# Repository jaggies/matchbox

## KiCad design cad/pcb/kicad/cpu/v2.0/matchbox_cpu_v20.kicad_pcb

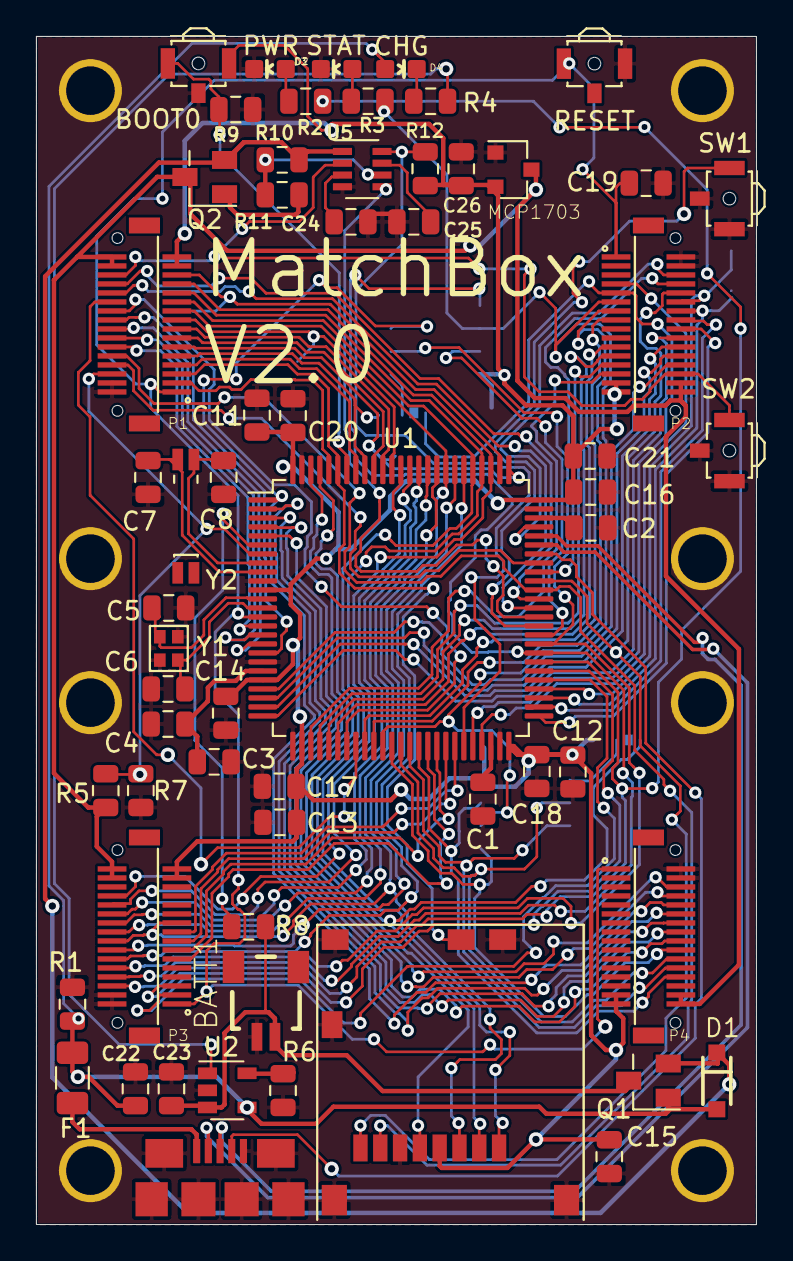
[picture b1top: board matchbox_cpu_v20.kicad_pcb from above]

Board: 6 copper layers, 40.0 x 66.0 mm, 75 parts (0 on the bottom side), 107 nets.

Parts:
BATT1: SM02B-SRSS-TBS; SM02B-SRSS-TB
C1, C2: 2.2uF; C_0805_2012Metric
C3, C9, C10, C11, C12, C13, C15, C21, C25, C26: 1uF; C_0805_2012Metric
C4, C14, C16, C17, C18, C19, C20: 0.1uF; C_0805_2012Metric
C5, C6: 4pF; C_0805_2012Metric
C7, C8: 8pF; C_0805_2012Metric
C22, C23: 10uF; C_0805_2012Metric
C24: .033uF; C_0805_2012Metric
D1: MBR120; SOD-123
D2: PWR; LED-0603
D3: STAT; LED-0603
D4: CHG; LED-0603
F1: PTCTHERMISTOR1206; R_1206_3216Metric
JP1: BANK1_SEL; SolderJumper-3_P1.3mm_Bridged12_Pad1.0x1.5mm_NumberLabels
JP2: BANK2_SEL; SolderJumper-3_P1.3mm_Bridged12_Pad1.0x1.5mm_NumberLabels
P1, P2, P3, P4: DF12-32-DP
Q1, Q2: FDN360P; SuperSOT-3
R1, R6: 4.7k; R_0805_2012Metric
R2, R3, R4: 1k; R_0805_2012Metric
R5, R7, R9, R12: 10k; R_0805_2012Metric
R8, R10, R11: 100k; R_0805_2012Metric
SD1: MOLEX_MICROSD_PP
SW0: BOOT0; B3U-3100PM-B
SW1, SW2: B3U-3100PM-B
SW3: RESET; B3U-3100PM-B
TP1: VCC_3V3; TestPoint_Pad_D1.5mm
TP2: GND; TestPoint_Pad_D1.5mm
TP3: RESET; TestPoint_Pad_D1.5mm
TP4: SWDCLK/TCK; TestPoint_Pad_D1.5mm
TP5: SWDIO/TMS; TestPoint_Pad_D1.5mm
TP6: SWO/TDO; TestPoint_Pad_D1.5mm
TP7: TDI; TestPoint_Pad_D1.5mm
TP8: TX; TestPoint_Pad_D1.5mm
TP9: RX; TestPoint_Pad_D1.5mm
U1: STM32H753VITx; LQFP-100_14x14mm_P0.5mm
U2: MCP73831-2-OT; SOT-23-5
U3: BANK1; SOIC-8_3.9x4.9mm_P1.27mm
U4: BANK2; SOIC-8_3.9x4.9mm_P1.27mm
U5: LTC2954; SOT-23-8
U6: MCP1703; SOT-23
USB1: MICROUSB
Y1: 16MHz(9pF); ABM11
Y2: 32.768kHz (9pF); CRYSTAL-32KHZ-SMD_EPSON_MC146

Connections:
/BANK1_CS#: JP1.2, U3.1
/BANK2_CS#: JP2.2, U4.1
/BOOT0: R9.1, SW0.1, U1.94
/OSC32K_IN: C8.1, U1.8, Y2.P$2
/OSC32K_OUT: C7.1, U1.9, Y2.P$1
/OSC_IN: C5.1, U1.12, Y1.1
/OSC_OUT: C6.1, U1.13, Y1.3
/PA0: P2.26, U1.22
/PA1: P2.24, U1.23
/PA2: P2.22, U1.24
/PA3: P2.20, U1.25
/PA4: P2.27, U1.28
/PA5: P2.25, U1.29
/PA6: P2.23, U1.30
/PA7: P2.21, U1.31
/PA8: P2.8, U1.67
/PA9: P1.8, U1.68
/PA13: P2.6, TP5.1, U1.72
/PA14: P1.11, TP4.1, U1.76
/PA15: P1.27, TP7.1, U1.77
/PB0: P2.15, U1.34
/PB1: P2.13, U1.35
/PB2: P2.11, R3.2, U1.36, U3.6, U4.6
/PB3: P1.17, TP6.1, U1.89
/PB4: P1.15, U1.90
/PB5: P1.13, U1.91
/PB6: JP1.3, P1.9, U1.92
/PB7: P1.7, U1.93
/PB8: P1.5, SD1.DET, U1.95
/PB9: P1.3, U1.96
/PB10: JP1.1, P2.9, U1.46
/PB11: P2.7, U1.47
/PB12: P2.18, U1.51
/PB13: P2.16, U1.52
/PB14: P2.14, TP8.1, U1.53
/PB15: P2.12, TP9.1, U1.54
/PC0: P1.12, U1.15
/PC1: P1.14, U1.16
/PC2: P1.16, U1.17
/PC3: P1.18, U1.18
/PC4: P1.20, U1.32
/PC5: P1.22, U1.33
/PC6: P1.24, U1.63
/PC7: P1.26, U1.64
/PC8: P1.10, SD1.7, U1.65
/PC9: P2.10, SD1.8, U1.66
/PC10: P1.25, SD1.1, U1.78
/PC11: JP2.1, P1.23, SD1.2, U1.79
/PC12: P1.21, SD1.5, U1.80
/PC13: P1.6, R5.2, R7.1, U1.7
/PD0: P3.12, U1.81
/PD1: P3.14, U1.82
/PD2: P1.19, P3.16, P3.19, SD1.3, U1.83
/PD3: P3.18, U1.84
/PD4: P3.20, U1.85
/PD5: P3.22, U1.86
/PD6: P3.24, U1.87
/PD7: P3.26, U1.88
/PD8: P3.3, U1.55
/PD9: P3.5, U1.56
/PD10: P3.6, R2.2, U1.57
/PD11: P3.8, U1.58, U3.5
/PD12: P3.10, U1.59, U3.2
/PD13: U1.60, U3.7
/PD14: SW1.1, U1.61
/PD15: U1.62, U5.5
/PE0: P4.6, U1.97
/PE1: P4.8, U1.98
/PE2: P4.10, U1.1, U3.3
/PE3: P4.12, U1.2
/PE4: P4.14, U1.3
/PE5: P4.16, U1.4
/PE6: P4.18, U1.5
/PE7: P4.20, U1.37, U4.5
/PE8: P4.22, U1.38, U4.2
/PE9: P4.24, U1.39, U4.3
/PE10: P4.26, U1.40, U4.7
/PE11: P3.11, U1.41
/PE12: P3.13, U1.42
/PE13: P3.15, U1.43
/PE14: P3.17, U1.44
/PE15: R12.1, U1.45, U5.8
/PWR_ON: P1.28, P2.28, SW2.1, U5.2
/RESET#: C19.1, P1.1, P2.1, P3.1, P4.1, SW3.1, TP3.1, U1.14
/STAT: R4.2, U2.1
/USB_D+: U1.71, USB1.3
/USB_D-: U1.70, USB1.2
/USB_ID: U1.69, USB1.4
/VBAT: BATT1.1, C23.1, Q1.3, R8.1, U2.3
/VCC: P1.30, P1.32, P2.30, P2.32, P3.30, P3.32, P4.30, P4.32, Q2.3, R5.1, U6.3
/VCC_3V3: C9.1, C10.1, C11.1, C12.1, C13.1, C14.1, C15.1, C16.1, C17.1, C18.1, C20.1, C21.1, C26.1, JP2.3, P1.29, P1.31, P2.29, P2.31, P3.29, P3.31, P4.29, P4.31, R12.2, SD1.4, SW0.2, TP1.1, U1.11, U1.21, U1.27, U1.50, U1.75, U1.100, U3.8, U4.8, U6.2
/VCC_BKUP: R8.2, U1.6
/VCC_SEL: D1.C, Q1.2, Q2.2, R10.1, U5.1
/VCC_USB: F1.1, USB1.1
/VCC_USBF: C22.1, D1.A, D4.A, F1.2, Q1.1, R1.1, U2.4
/VREF: C3.1, C4.1, U1.20
GND: BATT1.2, C1.1, C2.1, C3.2, C4.2, C5.2, C6.2, C7.2, C8.2, C9.2, C10.2, C11.2, C12.2, C13.2, C14.2, C15.2, C16.2, C17.2, C18.2, C19.2, C20.2, C21.2, C22.2, C23.2, C24.2, C25.2, C26.2, D2.C, D3.C, P1.2, P1.4, P2.2, P2.4, P3.2, P3.4, P4.2, P4.4, R1.2, R6.1, R7.2, R9.2, SD1.6, SD1.M1, SD1.M2, SD1.M3, SD1.M4, SD1.M5, SW0.GND, SW1.2, SW1.GND, SW2.2, SW2.GND, SW3.2, TP2.1, U1.10, U1.19, U1.26, U1.49, U1.74, U1.99, U2.2, U3.4, U4.4, U5.4, U6.1, USB1.5, USB1.6, USB1.7, USB1.8, USB1.9, USB1.10, USB1.11, Y1.2, Y1.4
unnamed: C1.2, U1.48
unnamed: C2.2, U1.73
unnamed: C24.1, U5.3
unnamed: C25.1, U5.7
unnamed: D2.A, R2.1
unnamed: D3.A, R3.1
unnamed: D4.C, R4.1
unnamed: Q2.1, R11.1
unnamed: R6.2, U2.5
unnamed: R10.2, R11.2, U5.6

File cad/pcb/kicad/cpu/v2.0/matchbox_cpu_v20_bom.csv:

Comment,Designator,Footprint,LCSC
"SM02B-SRSS-TBS","BATT1","matchbox_cpu_v20:SM02B-SRSS-TB",""
"2.2uF","C1,C2","Capacitor_SMD:C_0805_2012Metric",""
"0.1uF","C4,C14,C16,C17,C18,C19,C20","Capacitor_SMD:C_0805_2012Metric",""
"10uF","C22,C23","Capacitor_SMD:C_0805_2012Metric",""
".033uF","C24","Capacitor_SMD:C_0805_2012Metric",""
"1uF","C3,C9,C10,C11,C12,C13,C15,C21,C25,C26","Capacitor_SMD:C_0805_2012Metric",""
"4pF","C5,C6","Capacitor_SMD:C_0805_2012Metric",""
"8pF","C7,C8","Capacitor_SMD:C_0805_2012Metric",""
"MBR120","D1","Diode_SMD:D_SOD-123","C223608"
"CHG","D4","LED_SMD:LED_0603_1608Metric"," C72043"
"PTCTHERMISTOR1206","F1","Resistor_SMD:R_1206_3216Metric","C69688"
"BANK1_SEL","JP1","Jumper:SolderJumper-3_P1.3mm_Bridged12_Pad1.0x1.5mm_NumberLabels",""
"BANK2_SEL","JP2","Jumper:SolderJumper-3_P1.3mm_Bridged12_Pad1.0x1.5mm_NumberLabels",""
"PWR","LED2","LED_SMD:LED_0603_1608Metric",""
"STAT","LED3","LED_SMD:LED_0603_1608Metric"," C72043"
"DF12-32-DP","P1,P2,P3,P4","matchbox_cpu_v20:DF12-32-DP",""
"FDN360P","Q1,Q2","Package_TO_SOT_SMD:SuperSOT-3","C124463"
"1k","R2,R3,R4","Resistor_SMD:R_0805_2012Metric",""
"4.7k","R1,R6","Resistor_SMD:R_0805_2012Metric",""
"100k","R8,R10,R11","Resistor_SMD:R_0805_2012Metric",""
"10k","R5,R7,R9,R12","Resistor_SMD:R_0805_2012Metric",""
"MOLEX_MICROSD_PP","SD1","matchbox_ble_v01:MOLEX_MICROSD_PP","C429846"
"BOOT0","SW0","matchbox_cpu_v20:B3U-3100PM-B",""
"B3U-3100PM-B","SW1,SW2","matchbox_cpu_v20:B3U-3100PM-B",""
"RESET","SW3","matchbox_cpu_v20:B3U-3100PM-B",""
"VCC_3V3","TP1","TestPoint:TestPoint_Pad_D1.5mm",""
"GND","TP2","TestPoint:TestPoint_Pad_D1.5mm",""
"RESET","TP3","TestPoint:TestPoint_Pad_D1.5mm",""
"SWDCLK/TCK","TP4","TestPoint:TestPoint_Pad_D1.5mm",""
"SWDIO/TMS","TP5","TestPoint:TestPoint_Pad_D1.5mm",""
"SWO/TDO","TP6","TestPoint:TestPoint_Pad_D1.5mm",""
"TDI","TP7","TestPoint:TestPoint_Pad_D1.5mm",""
"TX","TP8","TestPoint:TestPoint_Pad_D1.5mm",""
"RX","TP9","TestPoint:TestPoint_Pad_D1.5mm",""
"STM32H753VITx","U1","Package_QFP:LQFP-100_14x14mm_P0.5mm","C529058"
"MCP73831-2-OT","U2","Package_TO_SOT_SMD:SOT-23-5","C424093"
"BANK1","U3","Package_SO:SOIC-8_3.9x4.9mm_P1.27mm","C113767"
"BANK2","U4","Package_SO:SOIC-8_3.9x4.9mm_P1.27mm","C113767"
"LTC2954","U5","Package_TO_SOT_SMD:SOT-23-8","C683782"
"MCP1703","U6","Package_TO_SOT_SMD:SOT-23","C638602"
"MICROUSB","USB1","matchbox_cpu_v20:MICROUSB","C132564"
"16MHz(9pF)","Y1","matchbox_cpu_v20:ABM11"," C13738"
"32.768kHz (9pF)","Y2","matchbox_cpu_v20:CRYSTAL-32KHZ-SMD_EPSON_MC146"," C15482"

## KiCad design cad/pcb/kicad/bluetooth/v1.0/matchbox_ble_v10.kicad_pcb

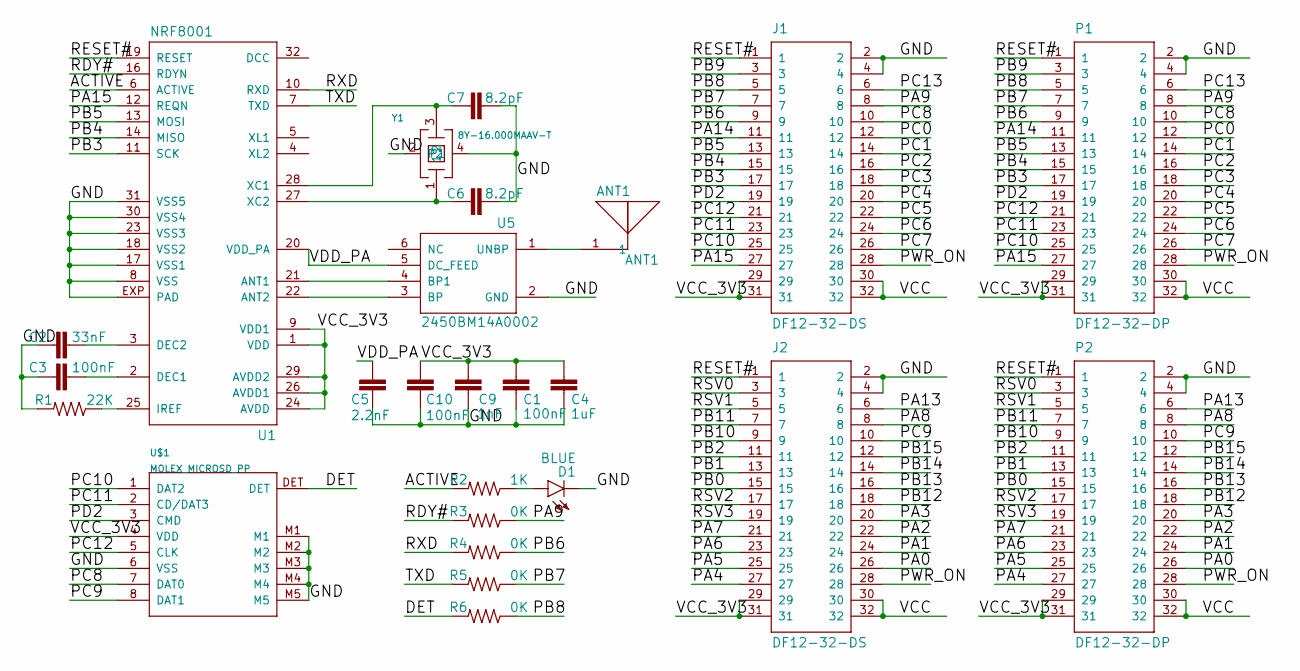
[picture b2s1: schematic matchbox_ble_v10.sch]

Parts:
ANT1: ANT1; 2450AT18A100; PARTNO AS-ITM-00132
C1, C3, C10: 100nF; 0402-CAP; MPN 1C20Z5U104M050B
C2: 33nF; 0402-CAP
C4: 1uF; 0805
C5: 2.2nF; 0402-CAP
C6, C7: 8.2pF; 0402-CAP
C9: 1nF; 0402-CAP
D1: BLUE; LED-0603
J1, J2: DF12-32-DS
P1, P2: DF12-32-DP
R1: 22K; 0402-RES
R2: 1K; 0805
R3, R4, R5, R6: 0K; 0805
U1: NRF8001; ATMEL_QFN32
U5: 2450BM14A0002
U$1: MOLEX_MICROSD_PP
Y1: 8Y-16.000MAAV-T; ABM11; PARTNO AS-ITM-00228

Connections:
/ACTIVE: R2.2, U1.6 (ACTIVE)
/DET: R6.2, U$1.DET
/GND: C1.2, C2.2, C3.2, C4.2, C5.2, C6.2, C7.2, C9.2, C10.2, D1.C, J1.2, J1.4, J2.2, J2.4, P1.2, P1.4, P2.2, P2.4, R1.2, U1.8 (VSS), U1.17 (VSS1), U1.18 (VSS2), U1.23 (VSS3), U1.30 (VSS4), U1.31 (VSS5), U1.EXP (PAD), U5.2 (GND), U$1.6 (VSS), U$1.M1, U$1.M2, U$1.M3, U$1.M4, U$1.M5, Y1.2, Y1.4 (P1)
/PA0: J2.26, P2.26
/PA1: J2.24, P2.24
/PA2: J2.22, P2.22
/PA3: J2.20, P2.20
/PA4: J2.27, P2.27
/PA5: J2.25, P2.25
/PA6: J2.23, P2.23
/PA7: J2.21, P2.21
/PA8: J2.8, P2.8
/PA9: J1.8, P1.8, R3.1
/PA13: J2.6, P2.6
/PA14: J1.11, P1.11
/PA15: J1.27, P1.27, U1.12 (REQN)
/PB0: J2.15, P2.15
/PB1: J2.13, P2.13
/PB2: J2.11, P2.11
/PB3: J1.17, P1.17, U1.11 (SCK)
/PB4: J1.15, P1.15, U1.14 (MISO)
/PB5: J1.13, P1.13, U1.13 (MOSI)
/PB6: J1.9, P1.9, R4.1
/PB7: J1.7, P1.7, R5.1
/PB8: J1.5, P1.5, R6.1
/PB9: J1.3, P1.3
/PB10: J2.9, P2.9
/PB11: J2.7, P2.7
/PB12: J2.18, P2.18
/PB13: J2.16, P2.16
/PB14: J2.14, P2.14
/PB15: J2.12, P2.12
/PC0: J1.12, P1.12
/PC1: J1.14, P1.14
/PC2: J1.16, P1.16
/PC3: J1.18, P1.18
/PC4: J1.20, P1.20
/PC5: J1.22, P1.22
/PC6: J1.24, P1.24
/PC7: J1.26, P1.26
/PC8: J1.10, P1.10, U$1.7 (DAT0)
/PC9: J2.10, P2.10, U$1.8 (DAT1)
/PC10: J1.25, P1.25, U$1.1 (DAT2)
/PC11: J1.23, P1.23, U$1.2 (CD/DAT3)
/PC12: J1.21, P1.21, U$1.5 (CLK)
/PC13: J1.6, P1.6
/PD2: J1.19, P1.19, U$1.3 (CMD)
/PWR_ON: J1.28, J2.28, P1.28, P2.28
/RDY#: R3.2, U1.16 (RDYN)
/RESET#: J1.1, J2.1, P1.1, P2.1, U1.19 (RESET)
/RSV0: J2.3, P2.3
/RSV1: J2.5, P2.5
/RSV2: J2.17, P2.17
/RSV3: J2.19, P2.19
/RXD: R4.2, U1.10 (RXD)
/TXD: R5.2, U1.7 (TXD)
/VCC: J1.30, J1.32, J2.30, J2.32, P1.30, P1.32, P2.30, P2.32
/VCC_3V3: C1.1, C4.1, C9.1, C10.1, J1.29, J1.31, J2.29, J2.31, P1.29, P1.31, P2.29, P2.31, U1.1 (VDD), U1.9 (VDD1), U1.24 (AVDD), U1.26 (AVDD1), U1.29 (AVDD2), U$1.4 (VDD)
/VDD_PA: C5.1, U1.20 (VDD_PA), U5.5 (DC_FEED)
unnamed: ANT1.1, U5.1 (UNBP)
unnamed: C2.1, U1.3 (DEC2)
unnamed: C3.1, U1.2 (DEC1)
unnamed: C6.1, U1.27 (XC2), Y1.1
unnamed: C7.1, U1.28 (XC1), Y1.3 (2)
unnamed: D1.A, R2.1
unnamed: R1.1, U1.25 (IREF)
unnamed: U1.21 (ANT1), U5.4 (BP1)
unnamed: U1.22 (ANT2), U5.3 (BP)

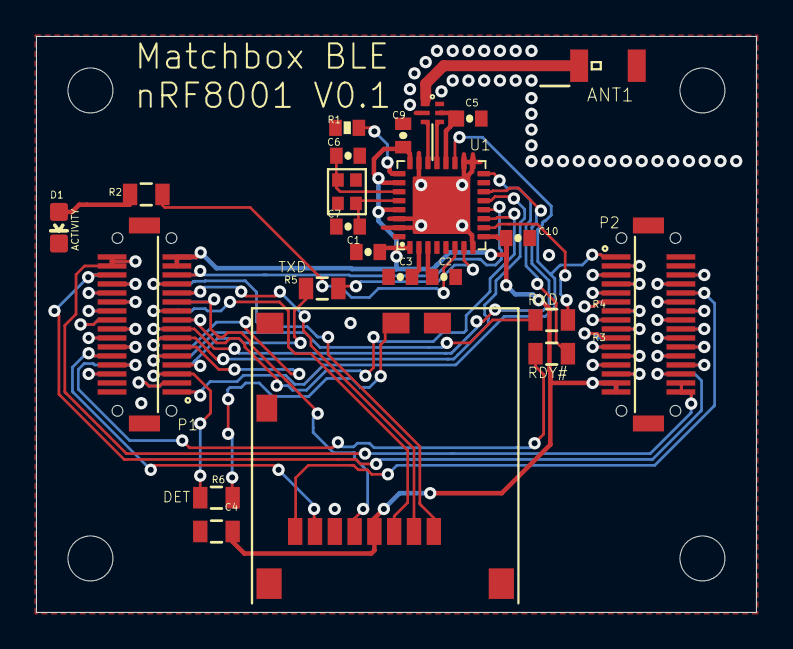
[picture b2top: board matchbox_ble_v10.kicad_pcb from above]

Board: 2 copper layers, 40.0 x 32.0 mm, 29 parts (0 on the bottom side), 68 nets.

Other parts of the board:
@HOLE0, @HOLE1, @HOLE2, @HOLE3: (no value)

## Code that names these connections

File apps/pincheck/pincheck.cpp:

/*
 * pincheck.cpp
 *
 *  Created on: Jul 15, 2016
 *      Author: jmiller
 */

#include <cstdio>
#include "matchbox.h"
#include "util.h"
#include "board.h"

uint64_t pups;
uint64_t drivers;
uint64_t receivers;
osThreadId defaultTaskHandle;

/**
 * Check pins for short:
 * pullUpCheck: the state of all pins during the initial pull-up. Should be all ones.
 * driver: non-zero driver bit means pin affected another pin when driven
 * receiver: list of all pins affected from drivers.
 */
void checkIoPins(uint64_t* pullUpCheck, uint64_t* driver, uint64_t* receiver) {
    static const int pins[] = {
        PA0, PA1, PA2, PA3, PA4, PA5, PA6, PA7, PA8, PA9, PA10, PA11, PA12, PA13, PA14, PA15,
        PB0, PB1, PB2, PB3, PB4, PB5, PB6, PB7, PB8, PB9, PB10, PB11, PB12, PB13, PB14, PB15,
        PC0, PC1, PC2, PC3, PC4, PC5, PC6, PC7, PC8, PC9, PC10, PC11, PC12, PC13, _PC14, _PC15 };

    for (int i = 0; i < sizeof(pins) / sizeof(pins[0]); i++) {
        pinInitInput(pins[i]); // init with pull-up
    }

    // Verify all pulled-up pins are logic '1'
    *pullUpCheck = 0ULL;
    for (int i = 0; i < Number(pins); i++) {
        *pullUpCheck |= readPin(pins[i]) ? (1ULL << pins[i]) : 0ULL;
    }

    // Pull one pin down at a time and look for other shorted pins
    *driver = *receiver = 0ULL;
    volatile int dly;
    for (int k = 0; k < Number(pins); k++) {
        if (k == PWR_KILL)
            continue; // don't kill the power!
        pinInitOutput(pins[k], 0); // pull it down
//        HAL_Delay(1); // wait for things to settle (10pF/10k = 100ns)
        dly= 100000; while (dly--) ;
        const int drv = pins[k];
        for (int i = 0; i < Number(pins); i++) {
            const int rcv = pins[i];
            if (drv != rcv && (readPin(rcv) ? 1ULL : 0ULL) != ((*pullUpCheck >> rcv) & 1ULL)) {
                // oops, unexpected pull down
                *driver |= 1ULL << drv; // driver
                *receiver |= 1ULL << rcv; // receiver
                break;
            }
        }
        pinInitInput(pins[k]); // pull it back up
    }
}

void printPinNames(uint64_t pins, uint64_t expected) {
    for (uint64_t i = 0; i < 48; i++) {
        if ((pins & (1LL << i)) != (expected << i)) {
            printf("P%c%d", "ABCD"[i>>4], i&0xf);
            if (i != 47) printf(" ");
        }
    }
}

void StartDefaultTask(void const * argument) {
    printf("HCLK: %d\n", HAL_RCC_GetHCLKFreq());
    printf("pups: %012llx (", pups);
    printPinNames(pups, 1);
    printf(")\n");

    printf("drivers: %012llx (", drivers);
    printPinNames(drivers, 0);
    printf(")\n");

    printf("receivers: %012llx (", receivers);
    printPinNames(receivers, 0);
    printf(")\n");

    // LED
    GPIO_InitTypeDef  GPIO_InitStruct = { 0 };
    GPIO_InitStruct.Pin = GPIO_PIN_2;
    GPIO_InitStruct.Mode = GPIO_MODE_OUTPUT_PP;
    GPIO_InitStruct.Pull = GPIO_NOPULL;
    GPIO_InitStruct.Speed = GPIO_SPEED_FREQ_VERY_HIGH;
    HAL_GPIO_Init(GPIOB, &GPIO_InitStruct);

    int count = 1;
    while (1) {
        HAL_GPIO_WritePin(GPIOB, GPIO_PIN_2, (count++ & 1) ? GPIO_PIN_SET : GPIO_PIN_RESET);
        HAL_Delay(500);
    }
}

void SystemClock_Config(void)
{

  RCC_OscInitTypeDef RCC_OscInitStruct;
  RCC_ClkInitTypeDef RCC_ClkInitStruct;
  __HAL_RCC_PWR_CLK_ENABLE();
  __HAL_PWR_VOLTAGESCALING_CONFIG(PWR_REGULATOR_VOLTAGE_SCALE1);

  RCC_OscInitStruct.OscillatorType = RCC_OSCILLATORTYPE_HSE;
  RCC_OscInitStruct.HSEState = RCC_HSE_ON;
  RCC_OscInitStruct.PLL.PLLState = RCC_PLL_ON;
  RCC_OscInitStruct.PLL.PLLSource = RCC_PLLSOURCE_HSE;
  RCC_OscInitStruct.PLL.PLLM = 8;
  RCC_OscInitStruct.PLL.PLLN = 72;
  RCC_OscInitStruct.PLL.PLLP = RCC_PLLP_DIV2;
  RCC_OscInitStruct.PLL.PLLQ = 3;
  HAL_RCC_OscConfig(&RCC_OscInitStruct);

  RCC_ClkInitStruct.ClockType = RCC_CLOCKTYPE_HCLK|RCC_CLOCKTYPE_SYSCLK
                              |RCC_CLOCKTYPE_PCLK1|RCC_CLOCKTYPE_PCLK2;
  RCC_ClkInitStruct.SYSCLKSource = RCC_SYSCLKSOURCE_PLLCLK;
  RCC_ClkInitStruct.AHBCLKDivider = RCC_SYSCLK_DIV1;
  RCC_ClkInitStruct.APB1CLKDivider = RCC_HCLK_DIV2;
  RCC_ClkInitStruct.APB2CLKDivider = RCC_HCLK_DIV1;
  HAL_RCC_ClockConfig(&RCC_ClkInitStruct, FLASH_LATENCY_2);
  HAL_SYSTICK_Config(HAL_RCC_GetHCLKFreq()/1000);
  HAL_SYSTICK_CLKSourceConfig(SYSTICK_CLKSOURCE_HCLK);

  /* SysTick_IRQn interrupt configuration */
  HAL_NVIC_SetPriority(SysTick_IRQn, 15, 0);
}

int main(void) {
    HAL_Init();
    SystemClock_Config();

    /* GPIO Ports Clock Enable */
    __HAL_RCC_GPIOC_CLK_ENABLE();
    __HAL_RCC_GPIOH_CLK_ENABLE();
    __HAL_RCC_GPIOA_CLK_ENABLE();
    __HAL_RCC_GPIOB_CLK_ENABLE();
    __HAL_RCC_GPIOD_CLK_ENABLE();

    checkIoPins(&pups, &drivers, &receivers);
    MatchBox* mb = new MatchBox();

    osThreadDef(defaultTask, StartDefaultTask, osPriorityNormal, 0, 2048);
    defaultTaskHandle = osThreadCreate(osThread(defaultTask), NULL);

    /* Start scheduler */
    osKernelStart();

    /* We should never get here as control is now taken by the scheduler */
    while (1)
        ;

    return 0;
}

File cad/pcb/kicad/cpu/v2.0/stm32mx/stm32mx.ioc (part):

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PA6.Mode=Full_Duplex_Master
Mcu.UserName=STM32H743VGTx
PB10.Mode=I2C
PC10.Signal=SPI3_SCK
PC12.Signal=SPI3_MOSI
PA11.Mode=OTG/Dual_Role_Device
PA15\ (JTDI).Signal=SPI3_NSS
PB11.Signal=I2C2_SDA
PB13.Signal=SPI2_SCK
PB15.Signal=SPI2_MOSI
PD9.Mode=Asynchronous
PD13.Signal=I2C4_SDA
PA14\ (JTCK/SWCLK).Signal=DEBUG_JTCK-SWCLK
PA15\ (JTDI).Mode=NSS_Signal_Hard_Output
PA12.Signal=USB_OTG_FS_DP
PE11.Mode=NSS_Signal_Hard_Output
PA4.Mode=NSS_Signal_Hard_Output
PB6.Signal=I2C1_SCL
PC7.Signal=USART6_RX
PB6.Mode=I2C
PD8.Signal=USART3_TX
PE1.Signal=UART8_TX
PE13.Signal=SPI4_MISO
PB14.Mode=Full_Duplex_Master
PA0.Mode=WakeUp0
PB7.Signal=I2C1_SDA
PA14\ (JTCK/SWCLK).Mode=Trace_Asynchronous_SW
PE13.Mode=Full_Duplex_Master
PE10.Signal=GPXTI10
PA0.Signal=PWR_WKUP0
Mcu.Package=LQFP100
PA6.Signal=SPI1_MISO
PB12.Mode=NSS_Signal_Hard_Output
PD12.Signal=I2C4_SCL
PA10.Signal=USB_OTG_FS_ID
PC11.Mode=Full_Duplex_Master
PB13.Mode=Full_Duplex_Master
PD15.Signal=GPXTI15
PA5.Mode=Full_Duplex_Master
PE12.Mode=Full_Duplex_Master
PA7.Mode=Full_Duplex_Master
PA13\ (JTMS/SWDIO).Mode=Trace_Asynchronous_SW
PA10.Mode=OTG/Dual_Role_Device
PC11.Signal=SPI3_MISO
PE1.Mode=Asynchronous
PC6.Signal=USART6_TX
PC10.Mode=Full_Duplex_Master
PD9.Signal=USART3_RX
PA9.Mode=Activate_VBUS_BCD
PB11.Mode=I2C
PB3\ (JTDO/TRACESWO).Signal=DEBUG_JTDO-SWO
PC6.Mode=Asynchronous
PA9.Signal=USB_OTG_FS_VBUS
PD13.Mode=I2C
PE11.Signal=SPI4_NSS
PD8.Mode=Asynchronous
PB10.Signal=I2C2_SCL
PB14.Signal=SPI2_MISO
PA5.Signal=SPI1_SCK
PC12.Mode=Full_Duplex_Master
board=custom
PB15.Mode=Full_Duplex_Master
PE14.Signal=SPI4_MOSI
PE15.Signal=GPIO_Output
PE14.Mode=Full_Duplex_Master
Mcu.Name=STM32H743VGTx
PE0.Signal=UART8_RX
PE12.Signal=SPI4_SCK
PD14.Signal=GPXTI14
PA4.Signal=SPI1_NSS
RCC.SYSCLKFreq_VALUE=64000000
PD12.Mode=I2C
PA12.Mode=OTG/Dual_Role_Device
PB7.Mode=I2C
PA11.Signal=USB_OTG_FS_DM
PB3\ (JTDO/TRACESWO).Mode=Trace_Asynchronous_SW
PC7.Mode=Asynchronous
PB12.Signal=SPI2_NSS
PE0.Mode=Asynchronous
PA13\ (JTMS/SWDIO).Signal=DEBUG_JTMS-SWDIO
PA7.Signal=SPI1_MOSI

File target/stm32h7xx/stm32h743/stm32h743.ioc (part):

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PA6.Mode=Full_Duplex_Master
Mcu.UserName=STM32H743VITx
PH0-OSC_IN\ (PH0).Signal=RCC_OSC_IN
PC12.Signal=SDMMC1_CK
PC10.Signal=SDMMC1_D2
PC15-OSC32_OUT\ (OSC32_OUT).Mode=LSE-External-Oscillator
PA9.GPIOParameters=GPIO_PuPd
PA11.Mode=Device_Only
PA15\ (JTDI).Signal=SPI3_NSS
PC13.GPIO_Label=VCC_MON
PB13.Signal=SPI2_SCK
PB15.Signal=SPI2_MOSI
PA15\ (JTDI).Mode=NSS_Signal_Hard_Input
PA12.Signal=USB_OTG_FS_DP
PD15.GPIOParameters=GPIO_PuPd,GPIO_Label
PA4.Mode=NSS_Signal_Hard_Output
PB6.Signal=USART1_TX
PB6.Mode=Asynchronous
PD10.GPIOParameters=GPIO_Label
PH1-OSC_OUT\ (PH1).Mode=HSE-External-Oscillator
RCC.HSE_VALUE=16000000
PB2.Signal=GPIO_Output
PB14.Mode=Full_Duplex_Master
PC9.Mode=SD_4_bits_Wide_bus
PB7.Signal=USART1_RX
PD14.GPIO_PuPd=GPIO_PULLUP
Mcu.Package=LQFP100
PA6.Signal=SPI1_MISO
PB12.Mode=NSS_Signal_Hard_Output
PD15.GPIO_PuPd=GPIO_PULLUP
PA10.Signal=USB_OTG_FS_ID
PC11.Mode=SD_4_bits_Wide_bus
PC14-OSC32_IN\ (OSC32_IN).Mode=LSE-External-Oscillator
PB13.Mode=Full_Duplex_Master
PD6.Signal=SPI3_MOSI
PH0-OSC_IN\ (PH0).Mode=HSE-External-Oscillator
PD15.Signal=GPIO_Input
PA5.Mode=Full_Duplex_Master
PD15.GPIO_Label=SW2
PB8.GPIOParameters=GPIO_PuPd,GPIO_Label
PA7.Mode=Full_Duplex_Master
PC11.Signal=SDMMC1_D3
PC13.Signal=GPIO_Analog
PC8.Signal=SDMMC1_D0
PB8.GPIO_PuPd=GPIO_PULLUP
PC10.Mode=SD_4_bits_Wide_bus
PD6.Mode=Full_Duplex_Master
PA9.GPIO_PuPd=GPIO_PULLUP
PH1-OSC_OUT\ (PH1).Signal=RCC_OSC_OUT
PE15.GPIOParameters=PinState,GPIO_Label
PD10.Signal=GPIO_Output
PB8.GPIO_Label=SD_DET
PE15.GPIO_Label=PWR_KILL
PB3\ (JTDO/TRACESWO).Signal=SPI3_SCK
PC15-OSC32_OUT\ (OSC32_OUT).Signal=RCC_OSC32_OUT
PB2.GPIOParameters=GPIO_Label
PA9.Signal=GPXTI9
PD10.GPIO_Label=LED2
PB14.Signal=SPI2_MISO
PD2.Mode=SD_4_bits_Wide_bus
PA5.Signal=SPI1_SCK
PC12.Mode=SD_4_bits_Wide_bus
board=custom
PB15.Mode=Full_Duplex_Master
PE15.Signal=GPIO_Output
PC13.GPIOParameters=GPIO_Label
PD14.GPIO_Label=SW1
PB4\ (NJTRST).Mode=Full_Duplex_Master
Mcu.Name=STM32H743VITx
PD14.Signal=GPIO_Input
PC8.Mode=SD_4_bits_Wide_bus
PA4.Signal=SPI1_NSS
PD14.GPIOParameters=GPIO_PuPd,GPIO_Label
RCC.SYSCLKFreq_VALUE=64000000
PA12.Mode=Device_Only
PC14-OSC32_IN\ (OSC32_IN).Signal=RCC_OSC32_IN
PA11.Signal=USB_OTG_FS_DM
PB7.Mode=Asynchronous
PB2.GPIO_Label=LED1
PB3\ (JTDO/TRACESWO).Mode=Full_Duplex_Master
PB8.Signal=GPXTI8
PC9.Signal=SDMMC1_D1
PD2.Signal=SDMMC1_CMD
PE15.PinState=GPIO_PIN_SET
PB12.Signal=SPI2_NSS
PA7.Signal=SPI1_MOSI
PB4\ (NJTRST).Signal=SPI3_MISO

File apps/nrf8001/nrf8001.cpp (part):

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    aci_state.aci_setup_info.setup_msgs = setup_msgs;
    aci_state.aci_setup_info.num_setup_msgs = NB_SETUP_MESSAGES;
    aci_state.aci_pins.board_name = BOARD_DEFAULT; //See boards.h for details
    aci_state.aci_pins.reqn_pin = PA15; // SS pin for nRF8001
    aci_state.aci_pins.rdyn_pin = PA9; // Interrupt pin from nRF8001
    aci_state.aci_pins.mosi_pin = PB5; // SPI data -> nRF8001
    aci_state.aci_pins.miso_pin = PB4; // SPI data <- nRF8001
    aci_state.aci_pins.sck_pin = PB3; // SPI clk
    aci_state.aci_pins.spi_clock_divider = 0; // TODO: Should be ~2MHz
    aci_state.aci_pins.reset_pin = UNUSED_PIN;
    aci_state.aci_pins.active_pin = UNUSED_PIN;
    aci_state.aci_pins.optional_chip_sel_pin = UNUSED_PIN;
    aci_state.aci_pins.interface_is_interrupt = false; // use interrupt handler for RDY#, else poll
    aci_state.aci_pins.interrupt_number = 1;

    // Reset nRF8001 with hardware line, if available.
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
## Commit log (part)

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2019-06-15 Add doc directory and ignore Debug.
2019-06-15 Reduce heap size (UNTESTED)
2019-06-15 Fix debugging printf
    error() only logs if debugging is enabled
    since it's pointless to log to a dead serial port.
2019-06-15 Minor optimization in LCD::clear().
2019-06-19 Remove rgb from calls in favor of setColor() method for speed.
2019-06-20 Expose font bitmap width/height
2020-05-25 Fix build on Linux
2020-05-25 Initial battery design
2020-05-25 Slightly deeper battery holder
2020-05-25 Battery holder with basic cuts (no extrusions)
2020-05-25 Added button cutouts
2020-05-25 Add cuts, but don't remove material yet
2020-05-25 More button cutout work
2020-05-25 Add retainer extrusion
2020-05-25 Switch to 1.5mm wall thickness
2020-05-25 More wall tweaks
2020-05-25 More battery compartment tweaks
2020-05-25 More final
2020-05-25 More tweaks
2020-05-25 Minor corrections after print verification
2020-05-25 More corrective tweaks
2020-05-25 Slight variation on tolerance relaxation
2020-05-25 Slight variation on tolerance relaxation.. part 2
2020-05-25 Add LCD cutouts to battery compartment
2020-05-25 Add buttons to new battery compartment
2020-05-25 Add battery wire cutout
2020-05-25 More tweaks to wire cutout
2020-05-25 Add display case
2020-05-25 Display case tweaks
2020-05-25 Minor display tweaks
2020-05-25 Switch to 1.9mm wall for display
2020-05-25 1.9mm wall cleanup
2020-05-25 Switch to 1.75mm wall thickness
2020-05-25 Switch to 1.75mm wall thickness... continued
2020-05-25 Display 1.5mm wall tweaks
2020-05-25 More 1.5mm wall display tweaks
2020-05-25 Shrink display retaining pins to 1.22mm
2020-05-25 More 1.75mm wall tweaks
2020-05-25 First corner piece
2020-05-25 Corner tinkering
2020-05-25 Initial corner with peg design
2020-05-25 Tweaked corner with pegs
2020-05-25 Add screw corner pieces with hole
2020-05-25 Tweak screw corners
2020-05-25 New corner design tweaks
2020-05-25 Relax tolerance with smaller 2.44mm pin
2020-05-25 Rename newbattery -> new_battery
2020-05-25 No battery case tweaks.
2020-05-25 Lower battery case with button correction
2020-05-25 Rename standard corner to peg-corner
2020-05-25 First jimduino version.
2020-05-25 Add LIPO charging circuit.
2020-05-25 Add more intelligent power switching and improve schematic layout.
2020-06-06 Release candidate 0
2020-06-06 Release Candidate 1
2020-06-06 Release Candidate 2
2020-06-06 New USB connector
2020-06-06 Final v1.0 cpu
2020-06-06 Use new side switches
2020-06-06 Change capacitance values. Final build?
2020-06-06 Add CPU version 1.2
2020-06-06 Add breakout board
2020-06-06 Tweak board
2020-06-06 Better routing
2020-06-06 Matchbox breakout board v1.0 (40x32mm)
2020-06-06 Tweaks to BOB v1.0
2020-06-06 Add matchbox BOB v1.1
2020-06-06 Initial matchbox display schematic & board
2020-06-06 Add display board v1.0
2020-06-06 Add display board v1.1
2020-06-06 BT tweaks
2020-06-06 More progress on v01 BLE
2020-06-06 Add VDDA supply (WIP)
2020-06-06 Final BLE board
2020-06-08 Define system clock to be 16MHz. Fix GCC warnings.
2020-06-08 Update flash script to use python3
2020-06-08 Use simpler raster operations to avoid using multiply per pixel.
2020-06-08 Add span() and special case clear performance for all black/all white
2020-06-08 Reuse stored already-stored pixels to fill the rest in clear().
2020-06-10 Minor LCD performance improvements
    - add span() primitive
    - move small routines to header for inlining
2020-06-10 Expose system clock configuration at runtime (Untested)
2020-06-11 Import STM32Cube_FW_F4_V1.25.0
2020-06-11 Get code roughly compiling.
    Import new ffconf.h
    Import new std32f4xx_hal_conf.h
    Fix renamed structures for SD files.
    Update USB_LL to use uint32_t size transfers (may fix old hang bug)
    Document hal_msp.c overloads
    LCDtest works, but is slow.
2020-06-11 Fix warnings about changed types.
2020-06-11 Add bridge directory and start porting sd code (WIP)
2020-06-11 All code now compiles and links.
    Threadtest and LCDtest both run, but the latter is really slow
2020-06-12 Create bridge device handlers for SD and USB (WIP)
    Hello.cpp works, but hangs after sending text.
2020-06-12 Clean up usbserial write operations.
2020-06-12 Change usb descriptor to "Generic"
2020-06-12 Fix sd_diskio variants.
2020-06-12 Enable wide bus operation in sdio_test (untested)
2020-06-13 Add linecoding support in attempt to get Linux to see something other than /dev/ttyACM*
2020-06-14 Fix USBSerial read (woot!)
    Formerly, the protocol wasn't implemented correctly, which caused
    an on-device hang when the USB FIFO was full.
    stdio::read() should now be able to read from the fifo (untested)
2020-06-14 Fix type-o in ReadBlocks
2020-06-14 Fix slow drawing on lcdtest by lowering SPI frequency
    Unknown why this only happens on STM32 V1.25. Presumably
    another IRQ is firing frequently and blocking this one.
    Investigation for another day...
2020-06-14 Set configuration closer to original matchbox config.
2020-06-15 Checkpoint:
    write appears to work if 1s delay is introduced between
    writes.
2020-06-16 Use LED to show callbacks instead of printf, which results in bad things
2020-06-16 sdio_dma_test works!!!
    The code required the addition of a loop to ensure non-overlapping
    DMA transfers to the SD cad. In short, follow the same code in
    sd_diskio_dma_rtos_bspv1.c which loops on BSP_SD_GetCardState()
    to check the transfer state after each operation.
2020-06-16 Improve sdio_dma_test to be more predictable.
    Read/write is expected to complete before returning, so do that.
2020-06-16 Update sdio_test with same completion logic as sdio_dma_test.
    Still has issues writing, especially on startup. Guessing these
    are related to the 'f415 errata about hardware flow control bugs.
2020-06-16 Fix BSP SDIO test case (DMA only)
2020-06-16 Got fatfs working again. Turns out the BSP completion routines weren't being called. May fix other tests as well (TODO)
2020-06-16 Clean up fatfs test printout
2020-06-16 Wait for SD card on startup for fatfs test.
2020-06-16 Bump CPU to 168MHz.
    Benchmarks on 16GB card:
    1.1MB write
    1.05MB read
2020-06-17 File cleanup.
2020-06-17 Add IDLE handler hook for apps to use to achieve lower power.
    Have LCD code yield the process while waiting for swapbuffers to occur.
    This cut the power in half for threadtest (from 72.9mA to 36.1mA)
2020-06-20 Use pre/post sleep hooks to further reduce power to 22.9mA
    Test conditions: matchbox CPU only (no daughter cards).
2020-06-20 Some further power improvements
    16MHz: 8.9mA
    24MHz: 9.1mA
    168MHz: 22.7mA
    Test condition: CPU only (no daughter cards)
2020-06-20 Get RTC running (WIP)
    Runs on internal oscillator, but way too fast.
2020-06-20 Handle newlines in font rendering
    Fix font rendering to know about max character width/height
2020-06-20 RTC app now prints to LCD instead of USB
2020-06-20 Improve putString/putChar routines to track raster position between calls.
    Should also improve performance. Still more to do.
2020-06-20 Use larger font in rtc test app.
    Also eliminate sleep waiting for USB since we don't use it anymore.
2020-06-20 USB delay require to prevent hang (fixme!)
2020-06-22 Hide PC14 and PC15 since they're used for the LSE oscillator
2020-06-22 Successfully initialized LSE (I think). At least no errros.
2020-06-22 Add freertos dependency to bletest
2020-06-22 LSE clock is probably working now, but needs a higher divisor than expected. The instructions in code want to be 1/1000th of the current value (32 instead of 32768)
2020-06-22 Save some power using larger divisor from datasheet.
    Also, ensure rtc app and main library use the same divisor sources.
2020-06-22 Add roboto-bold-32 font and use it in clock app
2020-06-22 Print in differnt fonts and ensure LCD command buffer gets updated in case pixels overflow into command area
2020-06-22 Run at super slow CPU speed to make performance improvements obvious.
2020-06-24 Only wait for vertical retrace if in double-buffer mode.
    Also, force-updates lcd SPI buffer in double buffer mode in
    case it gets overwritten by drawing commands. TODO: clip so this
    can't happen.
2020-06-24 More RTC refactoring
2020-06-24 Disable RTC backup domain after setting calendar.
2020-06-24 Attempt to fix time loss after every reset.
    Before this change, every reset caused the clock to loose nearly a
    second after reset. After this change, it still looses time unless
    we transition from the matchbox entrypoint to the bootloader
    to normal state. Likely memory state corryption.
    Will probably work fine with battery backup, but needs investigation.
2020-06-24 Use large font for date as well in RTC demo.
2020-06-24 Finally solve RTC losing 1 second per reset problem.
    The power-on reset flag was persisting since nobody clears it.
    So now we do...
2020-06-24 Always return 24h format so fatfs time is correct.
2020-06-24 Remove duplicate and global hrtc value.
2020-06-25 Add method to render to the front buffer where we don't really need double buffering.
2020-06-25 Add chip documentation
2020-06-26 Get 1 BLE channel working reliably showing sin wave.
2020-07-01 Add CPU v2 (WIP)
2020-07-01 More CPU v20 changes
2020-07-02 Routed CPU v2.0. Needs cleanup.
2020-07-02 Cleaned up decoupling caps and layout to maximize copper area.
2020-07-02 Add "tag-connect" JTAG connector to schematic
2020-07-02 Basic CPU v2.0 with connections and some cleanup work.
2020-07-03 Remove unnecessary RESET# pin pullup
2020-07-03 Add STM32CubeF4 as a submodule
2020-07-03 Add STM experimental repo as submodule
2020-07-03 Clean up CPUv2 component labels
2020-07-04 Ensure proper LCD startup by clearing line buffers to scan content.
2020-07-04 Hide EagleCad lock files.
2020-07-04 Remove links from lib/hal directory
    Jamfiles are now distributed in STM32CubeF4 directory.
2020-07-04 Add Vref bypass caps.
2020-07-04 Update footprints with KiCAD parts
2020-07-05 Improved bypass strategy: vias with local caps.
2020-07-05 Fix all labels and 3D rendering
2020-07-05 Add 3d crysta modesl and use correct Hirost connector on CPUv2
2020-07-05 Bypass cap improvements for STM32 part
2020-07-05 Minor ground plane improvements
2020-07-05 Fix all DRC errors with undefined courtyards
2020-07-06 P3 and P2 got swapped. Swap them back.
2020-07-06 Add D1 3d model back in.
2020-07-06 Set gerber parameters
2020-07-06 Updated RESET and BOOT0 since Kicad insists on changing the name every time I update the PCB
2020-07-07 Add place-holder SOIC-8 QPSI components
2020-07-07 Fully routed QSPI devices
2020-07-07 Add decoupling capacitors for QSPI parts
2020-07-07 More ground tweaking after attempting to add JTAG connector. Not enough room!
2020-07-08 Finishing touches
    - Move switches to +6mm from mounting holes
    - Use text instead of references for silkscreen
    - Add debug test points
    - Add test points for serial port 1
    - Clean up all silk screen labels
2020-07-08 Ignore H7 stuff in master until branch is merged.
2020-07-08 Fix misaligned fill polygons. They now match the cut outline.
2020-07-08 Ignore temporary gerber files
2020-07-08 Tune ground plane around SD card
2020-07-08 Minor cleanup before sending out for fab - Replace STM32H743VI with STM32H753VI which is currently easier to get - Fix mislabeled CN1 issue (now called BATT1) - Fix mislabeled wires on STM part for 1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
2020-07-09 Fix footprint issues on P1, P2 and P3 as well as CPU
    After uploading, I noticed some traces would hang off the respective
    pads, which will make soldering error-prone on these parts. Too late
    for this batch, maybe next.
2020-07-21 Checkpoint multi-target work
2020-07-21 Add digikey part numbers to schematic and create script to parse them into bom
2020-07-21 Move device-specific targets into target directories
2020-07-21 Refactor build to target separate directories for different devices.
    Compiles for target=STM32F4XX by default (untested)
    Compiles the H7 HAL driver but barfs on stm32f4xx-specific bridge code
    which will need to be partitioned.
2020-07-22 Add LCSC part numbers and take snapshot of working gerber settings
2020-07-24 Add script to generate header from cubemx pin csv file.
2020-07-24 Rename lib/compat to lib/arduino
2020-07-24 Use pin mapping from STMCubeMX tool
2020-07-24 Remove more device dependencies
    Also fixes race condition in build caused by multiple occurrences of port.c
2020-07-25 Fix H7 build (WIP)
2020-07-25 More device-specific build stuff for H7 vs F4
2020-07-25 Add configuration for stm32f415 and generate code
